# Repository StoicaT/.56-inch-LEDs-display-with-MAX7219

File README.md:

# .56-inch-LEDs-display-with-MAX7219
Building and testing  a module with 8 digits LEDs drived by MAX7219. 

This project aims to build and test an 8-digit LED module, 0.56 inches, drived by MAX2719. There are 2 variants, THT and SMD. 
PCBs are designed with KiCad program and are given together with Wiring Diagram and assembly details.
There is also a test program, which will be uploaded on an Arduino board and will allow a detailed visual check of the module.
More on:https://www.instructables.com/56inch-LEDs-Display-With-MAX7219/

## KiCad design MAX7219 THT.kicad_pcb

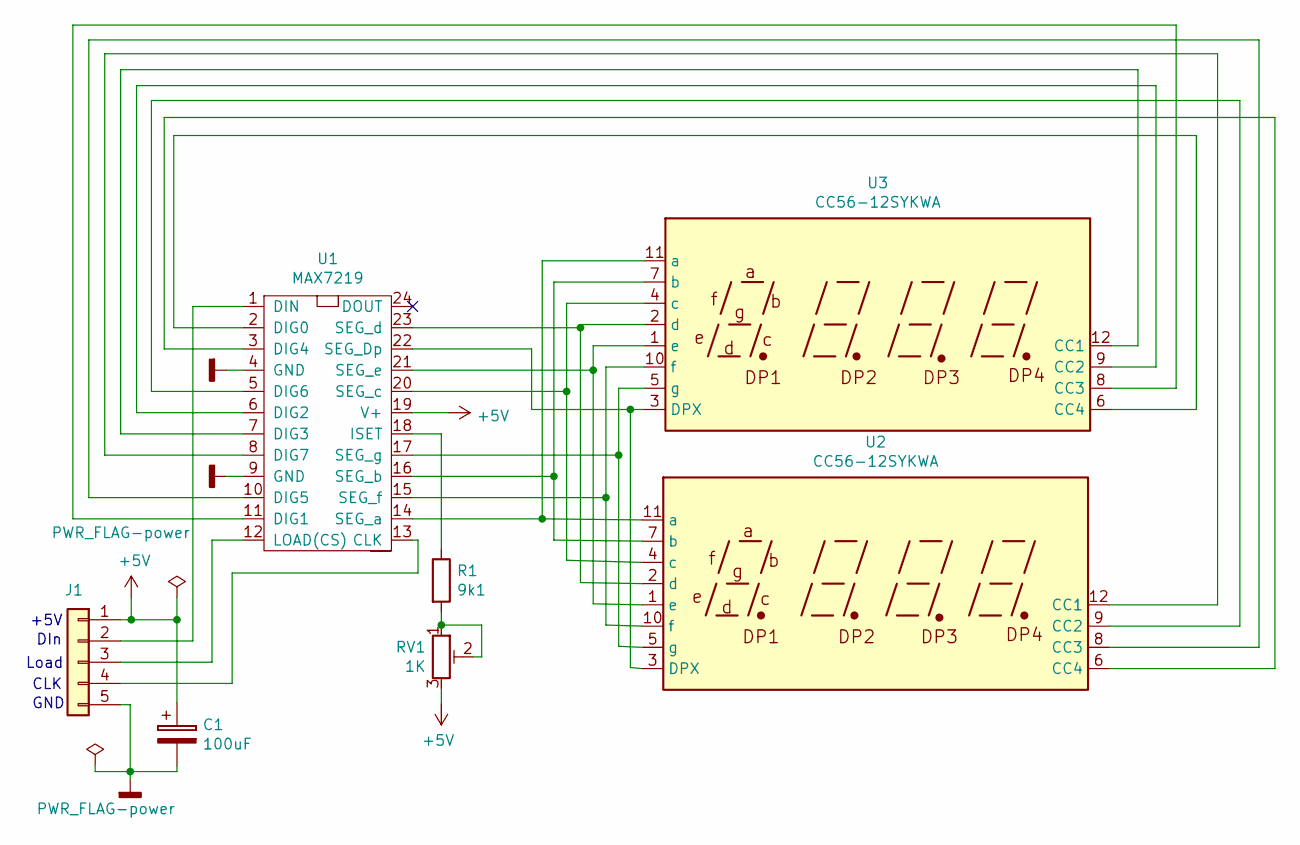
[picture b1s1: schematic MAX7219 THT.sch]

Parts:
C1: 100uF; CP_Radial_D7.5mm_P2.50mm
J1: Conn_01x05; PinHeader_1x05_P2.54mm_Vertical
R1: 9k1; R_Axial_DIN0207_L6.3mm_D2.5mm_P10.16mm_Horizontal
RV1: 1K; Potentiometer_Piher_PT-6-V_Vertical
U1: MAX7219
U2, U3: CC56-12SYKWA; CA56-12SYKWA

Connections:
+5V: C1.1, J1.1, RV1.3, U1.19 (V+)
GNDD: C1.2, J1.5, U1.4 (GND), U1.9 (GND)
unnamed: J1.2, U1.1 (DIN)
unnamed: J1.3, U1.12 (LOAD(CS))
unnamed: J1.4, U1.13 (CLK)
unnamed: R1.1, U1.18 (ISET)
unnamed: R1.2, RV1.1, RV1.2
unnamed: U1.2 (DIG0), U3.6 (CC4)
unnamed: U1.3 (DIG4), U2.6 (CC4)
unnamed: U1.5 (DIG6), U2.9 (CC2)
unnamed: U1.6 (DIG2), U3.9 (CC2)
unnamed: U1.7 (DIG3), U3.12 (CC1)
unnamed: U1.8 (DIG7), U2.12 (CC1)
unnamed: U1.10 (DIG5), U2.8 (CC3)
unnamed: U1.11 (DIG1), U3.8 (CC3)
unnamed: U1.14 (SEG_a), U2.11 (a), U3.11 (a)
unnamed: U1.15 (SEG_f), U2.10 (f), U3.10 (f)
unnamed: U1.16 (SEG_b), U2.7 (b), U3.7 (b)
unnamed: U1.17 (SEG_g), U2.5 (g), U3.5 (g)
unnamed: U1.20 (SEG_c), U2.4 (c), U3.4 (c)
unnamed: U1.21 (SEG_e), U2.1 (e), U3.1 (e)
unnamed: U1.22 (SEG_Dp), U2.3 (DPX), U3.3 (DPX)
unnamed: U1.23 (SEG_d), U2.2 (d), U3.2 (d)

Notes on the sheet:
+5V
GND
CLK
DIn
Load

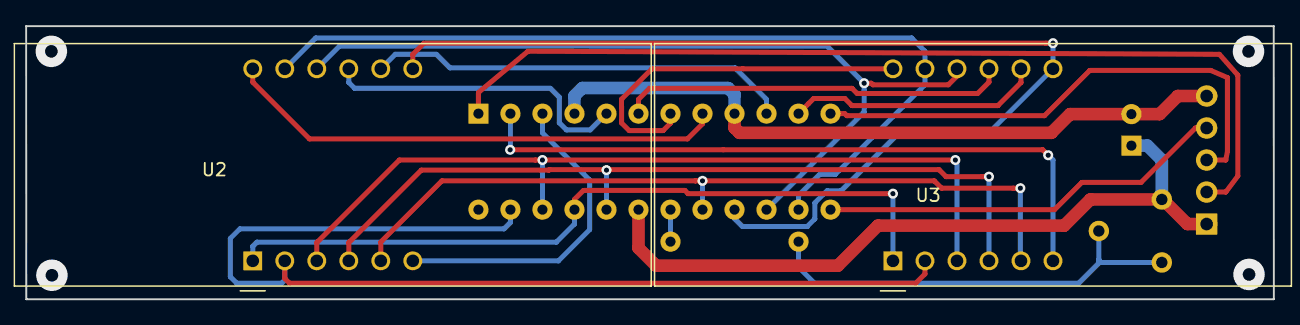
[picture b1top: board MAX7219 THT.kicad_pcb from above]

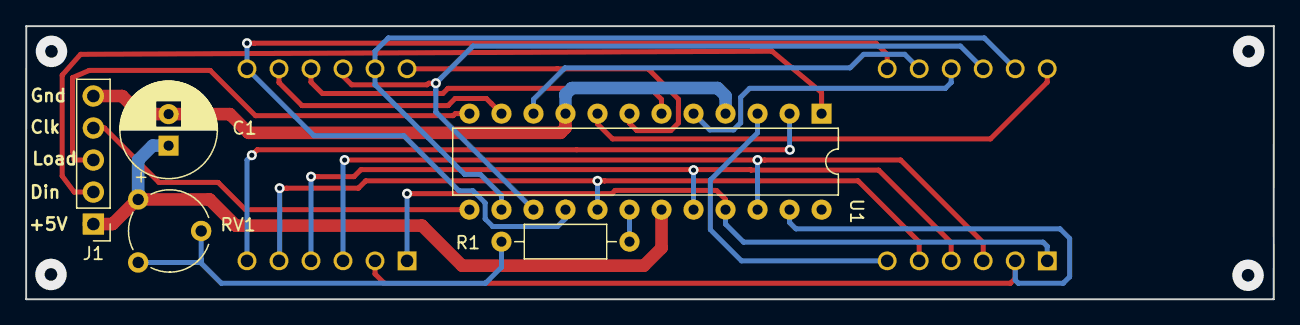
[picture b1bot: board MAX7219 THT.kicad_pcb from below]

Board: 2 copper layers, 99.0 x 21.7 mm, 7 parts (5 on the bottom side), 23 nets.

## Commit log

2021-05-06 Create MAX7219SMD
